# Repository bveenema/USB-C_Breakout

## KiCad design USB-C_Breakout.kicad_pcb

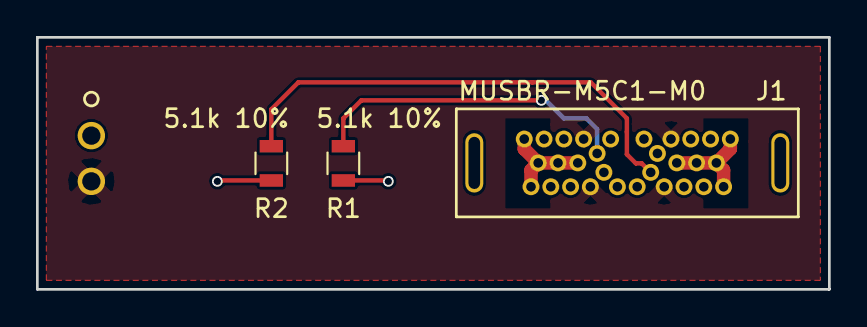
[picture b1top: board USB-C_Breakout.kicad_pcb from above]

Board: 2 copper layers, 44.0 x 14.0 mm, 4 parts (1 on the bottom side), 4 nets.

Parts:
J1: MUSBR-M5C1-M0; MUSBR-M5C1-X0
J2: 640455-2
R1, R2: 5.1k 10%; R_0805

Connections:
GND: J1.0, J1.A1, J1.A12, J1.B1, J1.B12, J1.G1, J1.G2, J1.G3, J1.G4, J1.G5, J1.G6, J2.1, R1.2, R2.2
unnamed: J1.A5, R1.1
unnamed: J1.B5, R2.1
VCC: J1.A4, J1.A9, J1.B4, J1.B9, J2.2

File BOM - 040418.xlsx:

| Reference | Quantity | Value | Package | Part Number | Alt Part Number
 | J1 | 1 | USB-C Conn | USB-C Conn | MUSBR-M5C1-M0 | N/A
 | J2 | 1 | AMP Conn | AMP Conn | 640455-2 | N/A
 | R1,R2 | 2 | 5.1K 10% | 0805 | RC0805FR-075K1L | RC2012F512CS

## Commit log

2018-04-03 Added .gitignore
2018-04-03 Updated Footprints
2018-04-04 Initial Release of Rev A
2018-04-04 Update PRO file (Stil Rev A)
2018-04-04 Generated new Gerbers (Still Rev A)

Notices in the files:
parts and their libraries:
Copyright 2016 Accelerated Designs. All rights reserved.
